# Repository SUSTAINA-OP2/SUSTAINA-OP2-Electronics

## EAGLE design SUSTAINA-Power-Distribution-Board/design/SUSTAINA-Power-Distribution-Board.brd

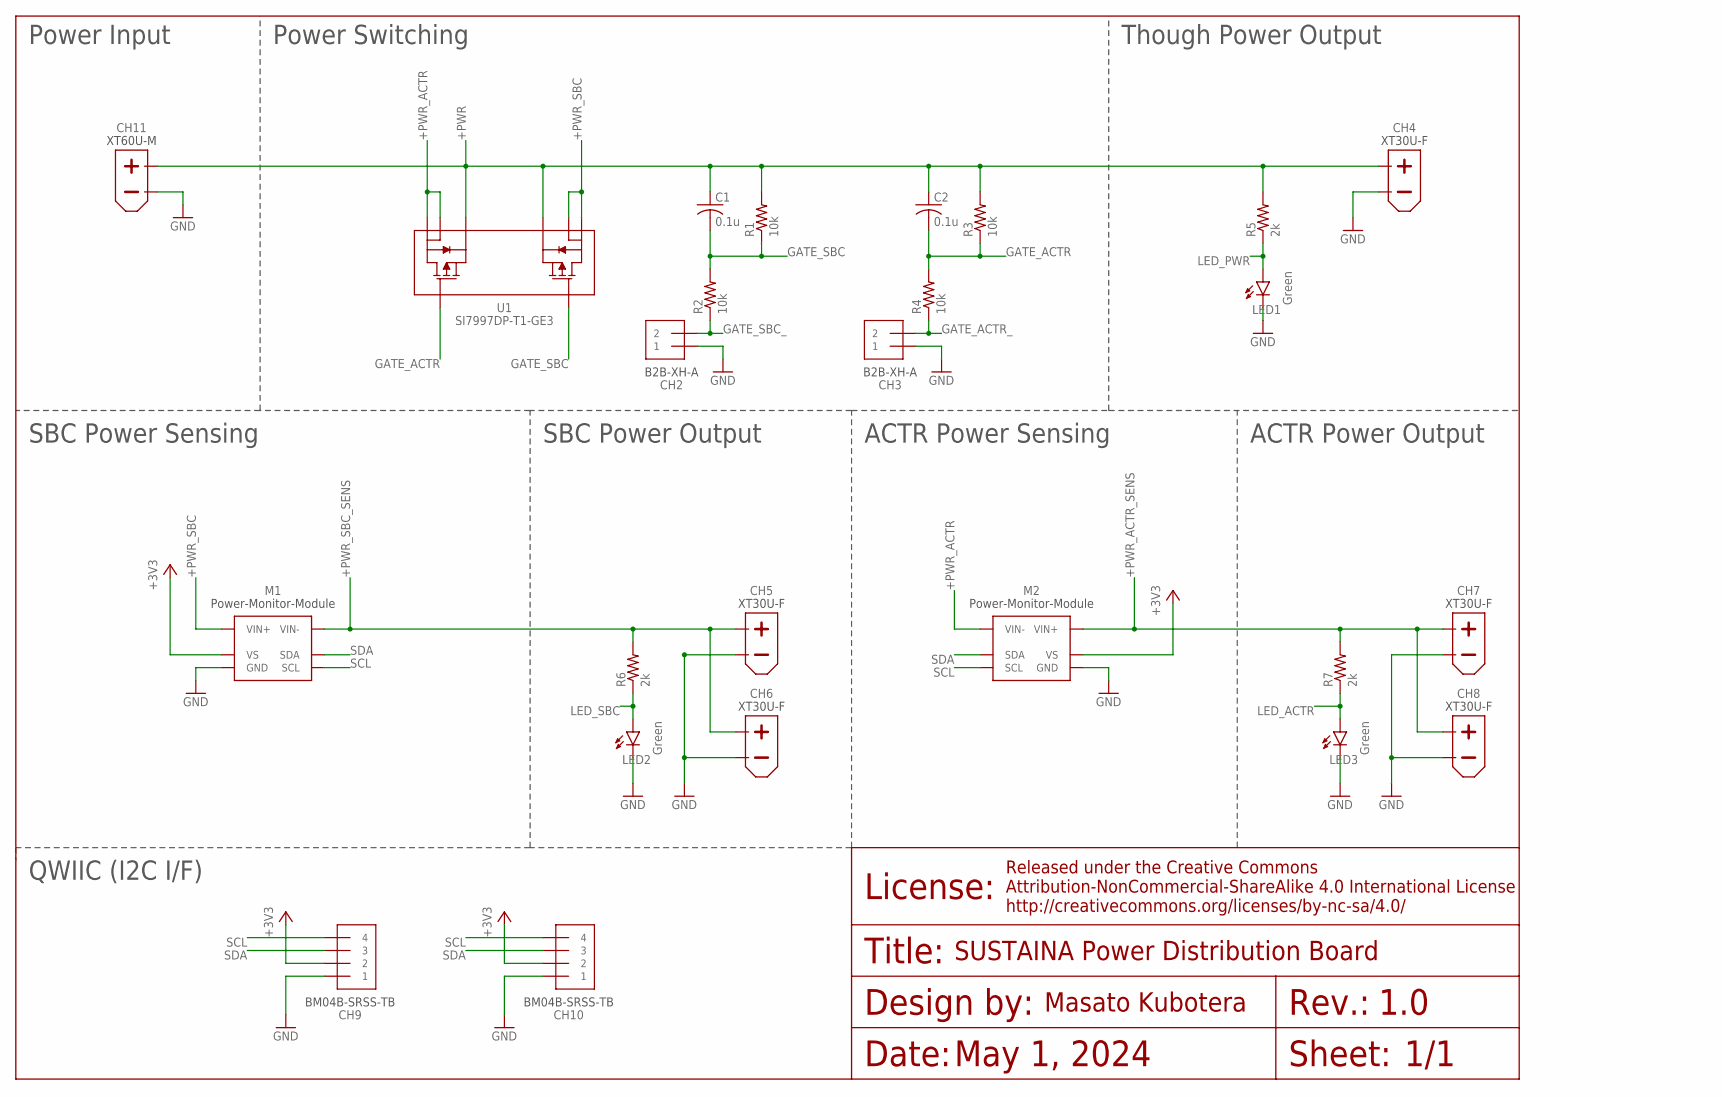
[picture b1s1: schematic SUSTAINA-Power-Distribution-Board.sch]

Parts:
C1, C2: 0.1u; C0603
CH2, CH3: B2B-XH-A
CH4, CH5, CH6, CH7, CH8: XT30U-F
CH9, CH10: BM04B-SRSS-TB
CH11: XT60U-M
LED1, LED2, LED3: Green; SML0603
M1, M2: POWER-MONITOR-MODULE
R1, R2, R3, R4: 10k; R0603
R5, R6, R7: 2k; R0603
U1: SI7997DP-T1-GE3; POWERPAK_SO-8_VIS

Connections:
+3V3: CH9.2, CH10.2, M1.VS, M2.VS
+PWR: C1.1, C2.1, CH4.+, CH11.+, R1.2, R3.2, R5.2, U1.1 (S1), U1.3 (S2)
+PWR_ACTR: M2.VIN-1 (VIN-), M2.VIN-2 (VIN-), M2.VIN-3 (VIN-), M2.VIN-4 (VIN-), M2.VIN-5 (VIN-), M2.VIN-6 (VIN-), M2.VIN-7 (VIN-), M2.VIN-8 (VIN-), M2.VIN-9 (VIN-), M2.VIN-10 (VIN-), U1.7 (D1), U1.8 (D1_2)
+PWR_ACTR_SENS: CH7.+, CH8.+, M2.VIN+1 (VIN+), M2.VIN+2 (VIN+), M2.VIN+3 (VIN+), M2.VIN+4 (VIN+), M2.VIN+5 (VIN+), M2.VIN+6 (VIN+), M2.VIN+7 (VIN+), M2.VIN+8 (VIN+), M2.VIN+9 (VIN+), M2.VIN+10 (VIN+), R7.2
+PWR_SBC: M1.VIN+1 (VIN+), M1.VIN+2 (VIN+), M1.VIN+3 (VIN+), M1.VIN+4 (VIN+), M1.VIN+5 (VIN+), M1.VIN+6 (VIN+), M1.VIN+7 (VIN+), M1.VIN+8 (VIN+), M1.VIN+9 (VIN+), M1.VIN+10 (VIN+), U1.5 (D2), U1.6 (D2_2)
+PWR_SBC_SENS: CH5.+, CH6.+, M1.VIN-1 (VIN-), M1.VIN-2 (VIN-), M1.VIN-3 (VIN-), M1.VIN-4 (VIN-), M1.VIN-5 (VIN-), M1.VIN-6 (VIN-), M1.VIN-7 (VIN-), M1.VIN-8 (VIN-), M1.VIN-9 (VIN-), M1.VIN-10 (VIN-), R6.2
GATE_ACTR: C2.2, R3.1, R4.2, U1.2 (G1)
GATE_ACTR_: CH3.2, R4.1
GATE_SBC: C1.2, R1.1, R2.2, U1.4 (G2)
GATE_SBC_: CH2.2, R2.1
GND: CH2.1, CH3.1, CH4.-, CH5.-, CH6.-, CH7.-, CH8.-, CH9.1, CH10.1, CH11.-, LED1.C, LED2.C, LED3.C, M1.GND, M2.GND
LED_ACTR: LED3.A, R7.1
LED_PWR: LED1.A, R5.1
LED_SBC: LED2.A, R6.1
SCL: CH9.4, CH10.4, M1.SCL, M2.SCL
SDA: CH9.3, CH10.3, M1.SDA, M2.SDA

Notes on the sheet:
1.0
1/1
May 1, 2024
SUSTAINA Power Distribution Board
Power Input
ACTR Power Sensing
SBC Power Sensing
QWIIC (I2C I/F)
Power Switching
Though Power Output
SBC Power Output
ACTR Power Output

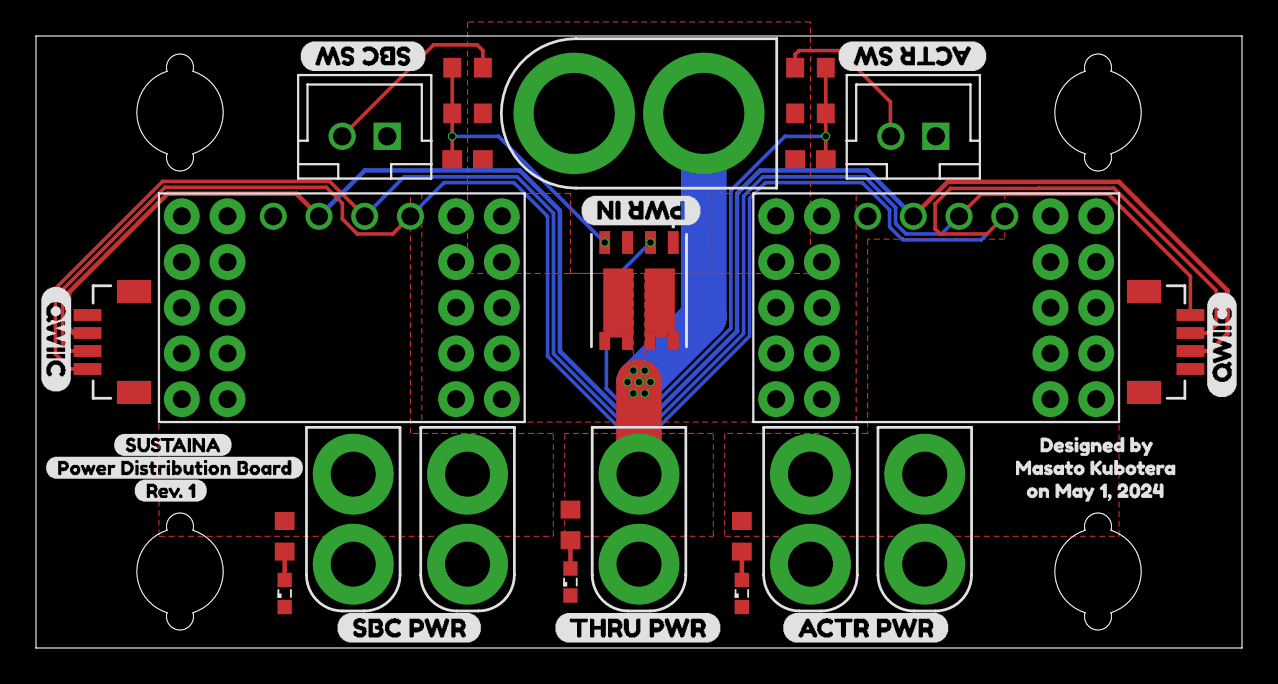
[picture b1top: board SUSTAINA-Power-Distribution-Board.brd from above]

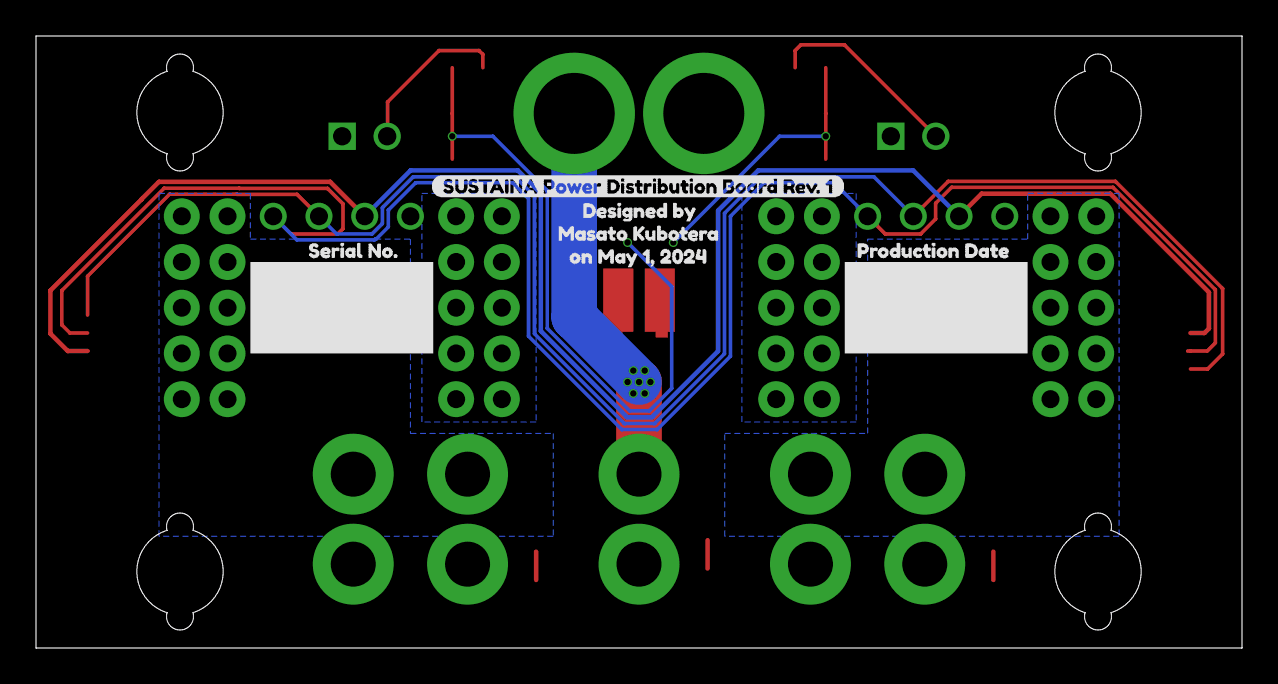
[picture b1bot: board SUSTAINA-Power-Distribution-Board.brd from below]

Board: 2 copper layers, 67.0 x 34.0 mm, 41 parts (4 on the bottom side), 16 nets.

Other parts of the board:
U$1, U$8: QWIIC
U$2: ACTR_SW
U$3: SBC_SW
U$4: ACTR_PWR
U$5: THRU_PWR
U$6: SBC_PWR
U$7: PWR_IN
U$9: PRODUCTION_DATE-0.03
U$10: SUSTAINA_POWER_DISTRIBUTION_BOARD_REV#_1-0.03
U$11, U$12: DESIGNED_BY_MASATO_KUBOTERA_ON_MAY_1-COLUMN
U$14: REV#_1-0.03
U$15: SUSTAINA-0.03
U$18: POWER_DISTRIBUTION_BOARD-0.03
U$19: SERIAL_NO#-0.03

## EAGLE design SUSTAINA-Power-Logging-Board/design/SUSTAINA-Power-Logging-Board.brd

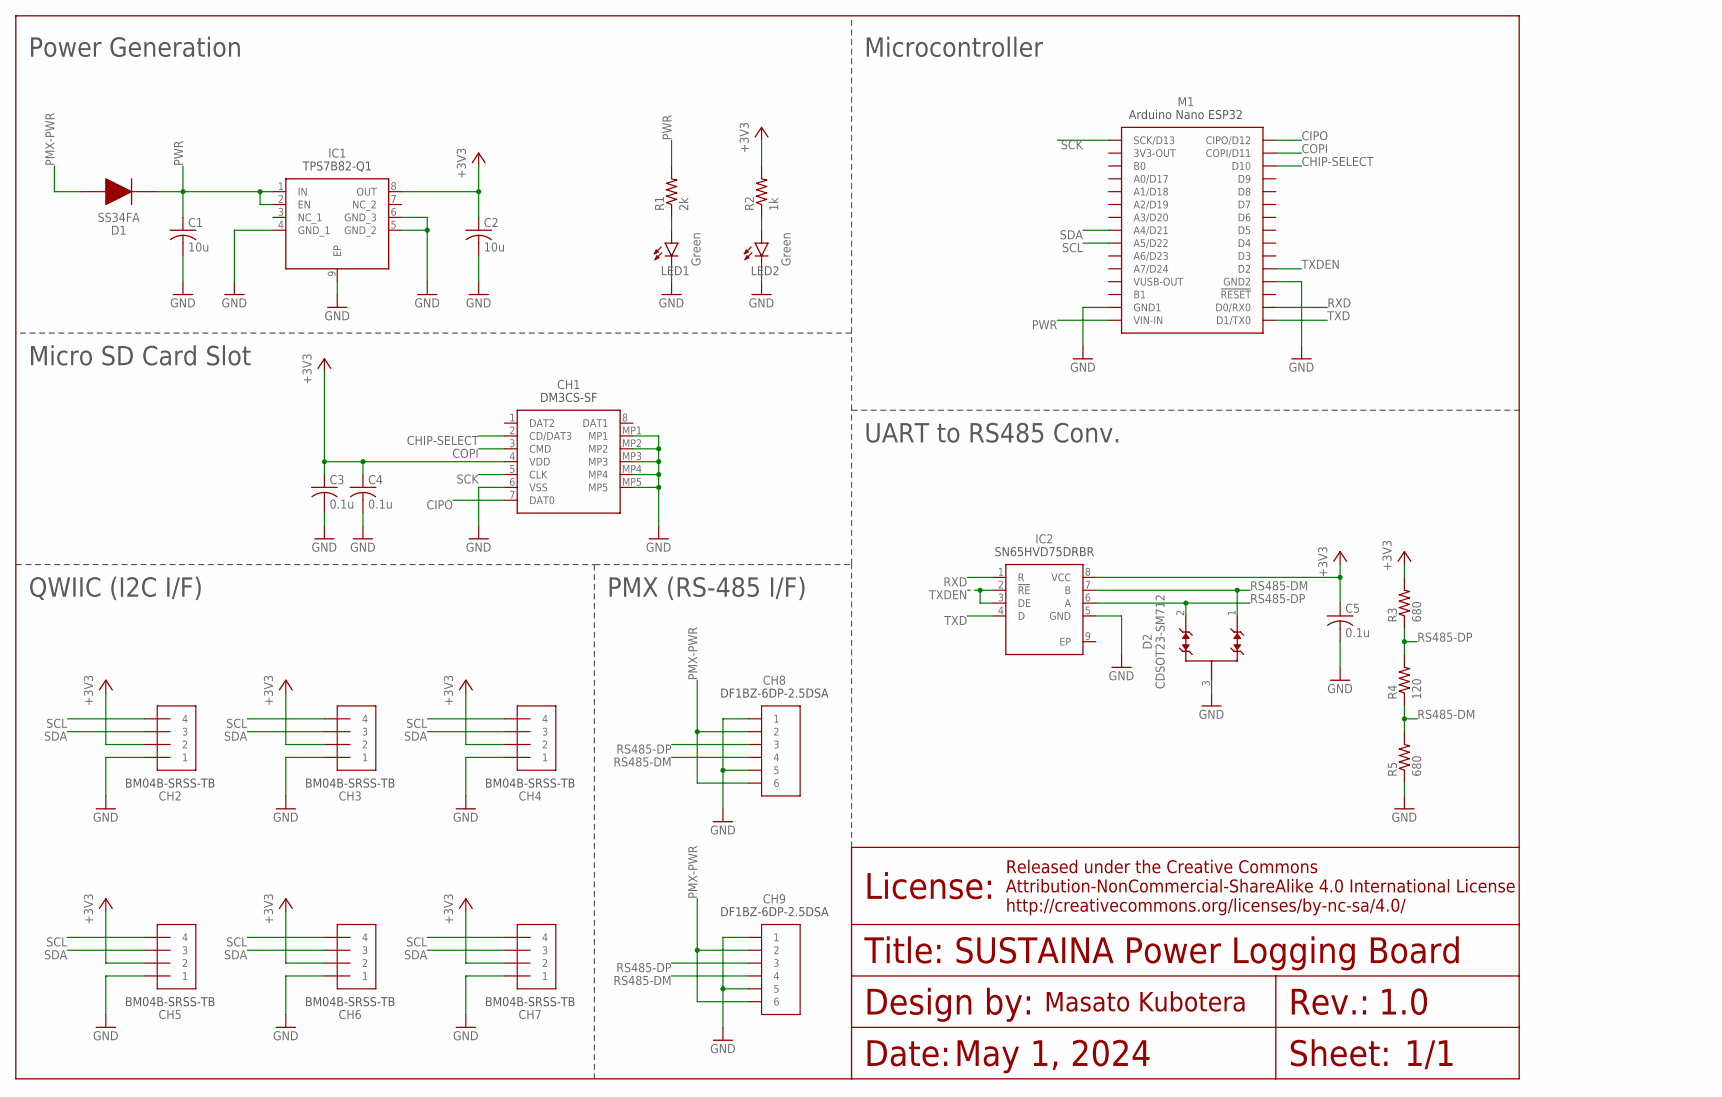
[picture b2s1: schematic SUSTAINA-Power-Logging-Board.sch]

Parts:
C1, C2: 10u; C0603
C3, C4, C5: 0.1u; C0603
CH1: DM3CS-SF
CH2, CH3, CH4, CH5, CH6, CH7: BM04B-SRSS-TB
CH8, CH9: DF1BZ-6DP-25DSA
D1: SS34FA
D2: CDSOT23-SM712; SOT-23-3
IC1: TPS7B82-Q1; SOP65P490X110-9N
IC2: SN65HVD75DRBR; SON65P300X300X100-9N
LED1, LED2: Green; SML0603
M1: NANO-ESP32
R1: 2k; R0603
R2: 1k; R0603
R3, R5: 680; R0603
R4: 120; R0603

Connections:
+3V3: C2.1, C3.1, C4.1, C5.1, CH1.4 (VDD), CH2.2, CH3.2, CH4.2, CH5.2, CH6.2, CH7.2, IC1.8 (OUT), IC2.8 (VCC), R2.2, R3.2
CHIP-SELECT: CH1.2 (CD/DAT3), M1.D10
CIPO: CH1.7 (DAT0), M1.CIPO/D12
COPI: CH1.3 (CMD), M1.COPI/D11
GND: C1.2, C2.2, C3.2, C4.2, C5.2, CH1.6 (VSS), CH1.MP1, CH1.MP2, CH1.MP3, CH1.MP4, CH1.MP5, CH2.1, CH3.1, CH4.1, CH5.1, CH6.1, CH7.1, CH8.1, CH8.5, CH9.1, CH9.5, D2.3, IC1.4 (GND_1), IC1.5 (GND_2), IC1.6 (GND_3), IC1.9 (EP), IC2.5 (GND), LED1.C, LED2.C, M1.GND1, M1.GND2, R5.1
LED-3V3: LED2.A, R2.1
LED-PWR: LED1.A, R1.1
PMX-PWR: CH8.2, CH8.6, CH9.2, CH9.6, D1.2
PWR: C1.1, D1.1, IC1.1 (IN), IC1.2 (EN), M1.VIN-IN, R1.2
RS485-DM: CH8.4, CH9.4, D2.1, IC2.7 (B), R4.1, R5.2
RS485-DP: CH8.3, CH9.3, D2.2, IC2.6 (A), R3.1, R4.2
RXD: IC2.1 (R), M1.D0/RX0
SCK: CH1.5 (CLK), M1.SCK/D13
SCL: CH2.4, CH3.4, CH4.4, CH5.4, CH6.4, CH7.4, M1.A5/D22
SDA: CH2.3, CH3.3, CH4.3, CH5.3, CH6.3, CH7.3, M1.A4/D21
TXD: IC2.4 (D), M1.D1/TX0
TXDEN: IC2.2 (!RE), IC2.3 (DE), M1.D2

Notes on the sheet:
Power Generation
Microcontroller
PMX (RS-485 I/F)
UART to RS485 Conv.
1.0
1/1
May 1, 2024
SUSTAINA Power Logging Board
Micro SD Card Slot
QWIIC (I2C I/F)

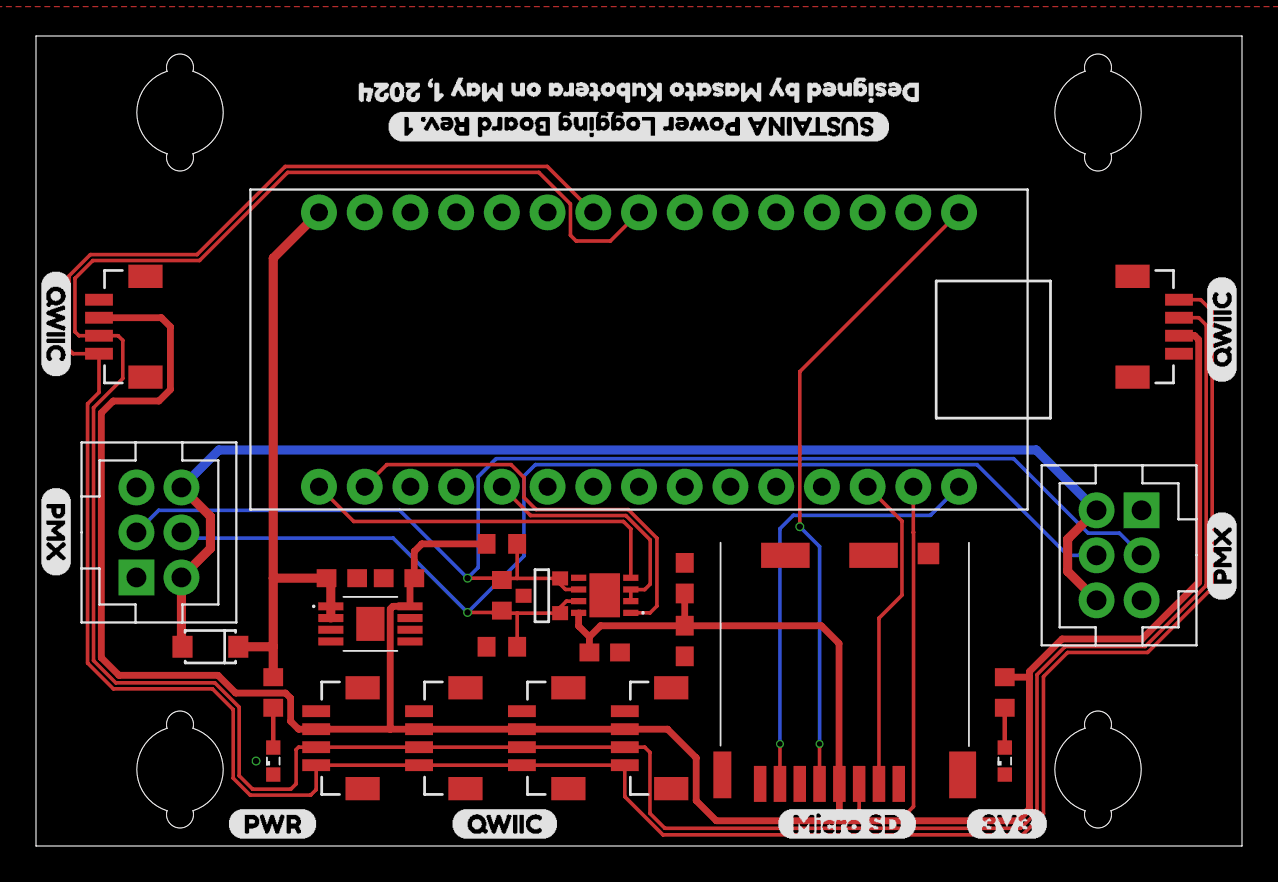
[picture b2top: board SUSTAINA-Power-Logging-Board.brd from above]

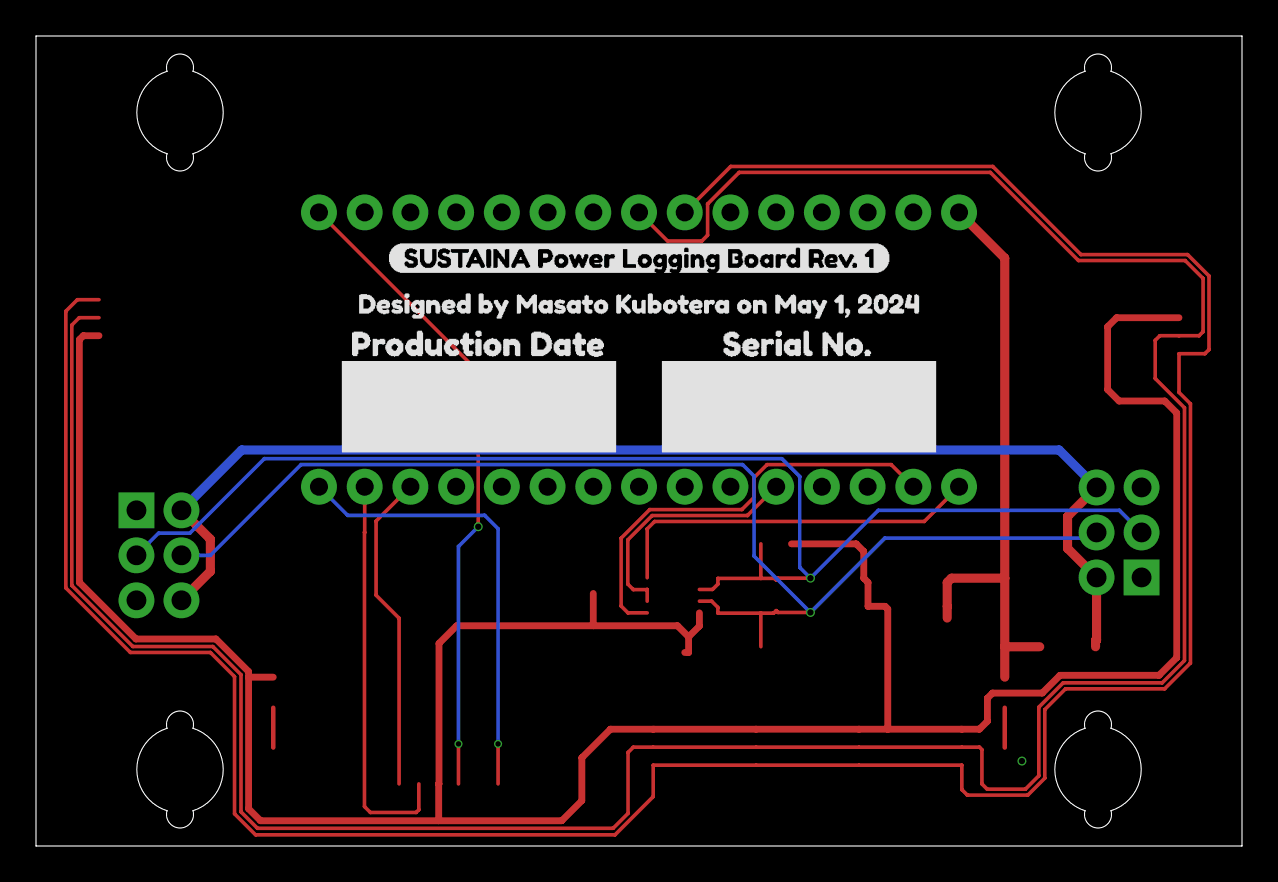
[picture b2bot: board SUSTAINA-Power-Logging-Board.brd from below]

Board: 2 copper layers, 67.0 x 45.0 mm, 40 parts (4 on the bottom side), 17 nets.

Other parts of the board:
U$1, U$12: PMX
U$2: 3V3
U$3: MICRO_SD
U$4, U$5, U$10: QWIIC
U$6: PRODUCTION_DATE0
U$7: SERIAL_NO#0
U$8, U$9: DESIGNED_BY_MASATO_KUBOTERA_ON_MAY_1
U$11, U$14: SUSTAINA_POWER_LOGGING_BOARD_REV#_1
U$13: PWR

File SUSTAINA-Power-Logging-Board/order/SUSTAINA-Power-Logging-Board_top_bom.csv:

Comment,Designator,Footprint,LCSC Part #
0.1u,C3 C4 C5,C0603,C80516
1k,R2,R0603,C22548
2k,R1,R0603,C105576
10u,C1 C2,C0603,C86275
120,R4,R0603,C114640
680,R3 R5,R0603,C112310
BM04B-SRSS-TB,CH2 CH3 CH4 CH5 CH6 CH7,BM04B-SRSS-TB,C160390
DM3CS-SF,CH1,DM3CS-SF,C202111
Green,LED1 LED2,SML0603,C2922668
SN65HVD75DRBR,IC2,SON65P300X300X100-9N,C98708
SS34FA,D1,SS34FA,C719833
TPS7B82-Q1,IC1,SOP65P490X110-9N,C5220182
CDSOT23-SM712,D2 ,CDSOT23-SM712,C404012

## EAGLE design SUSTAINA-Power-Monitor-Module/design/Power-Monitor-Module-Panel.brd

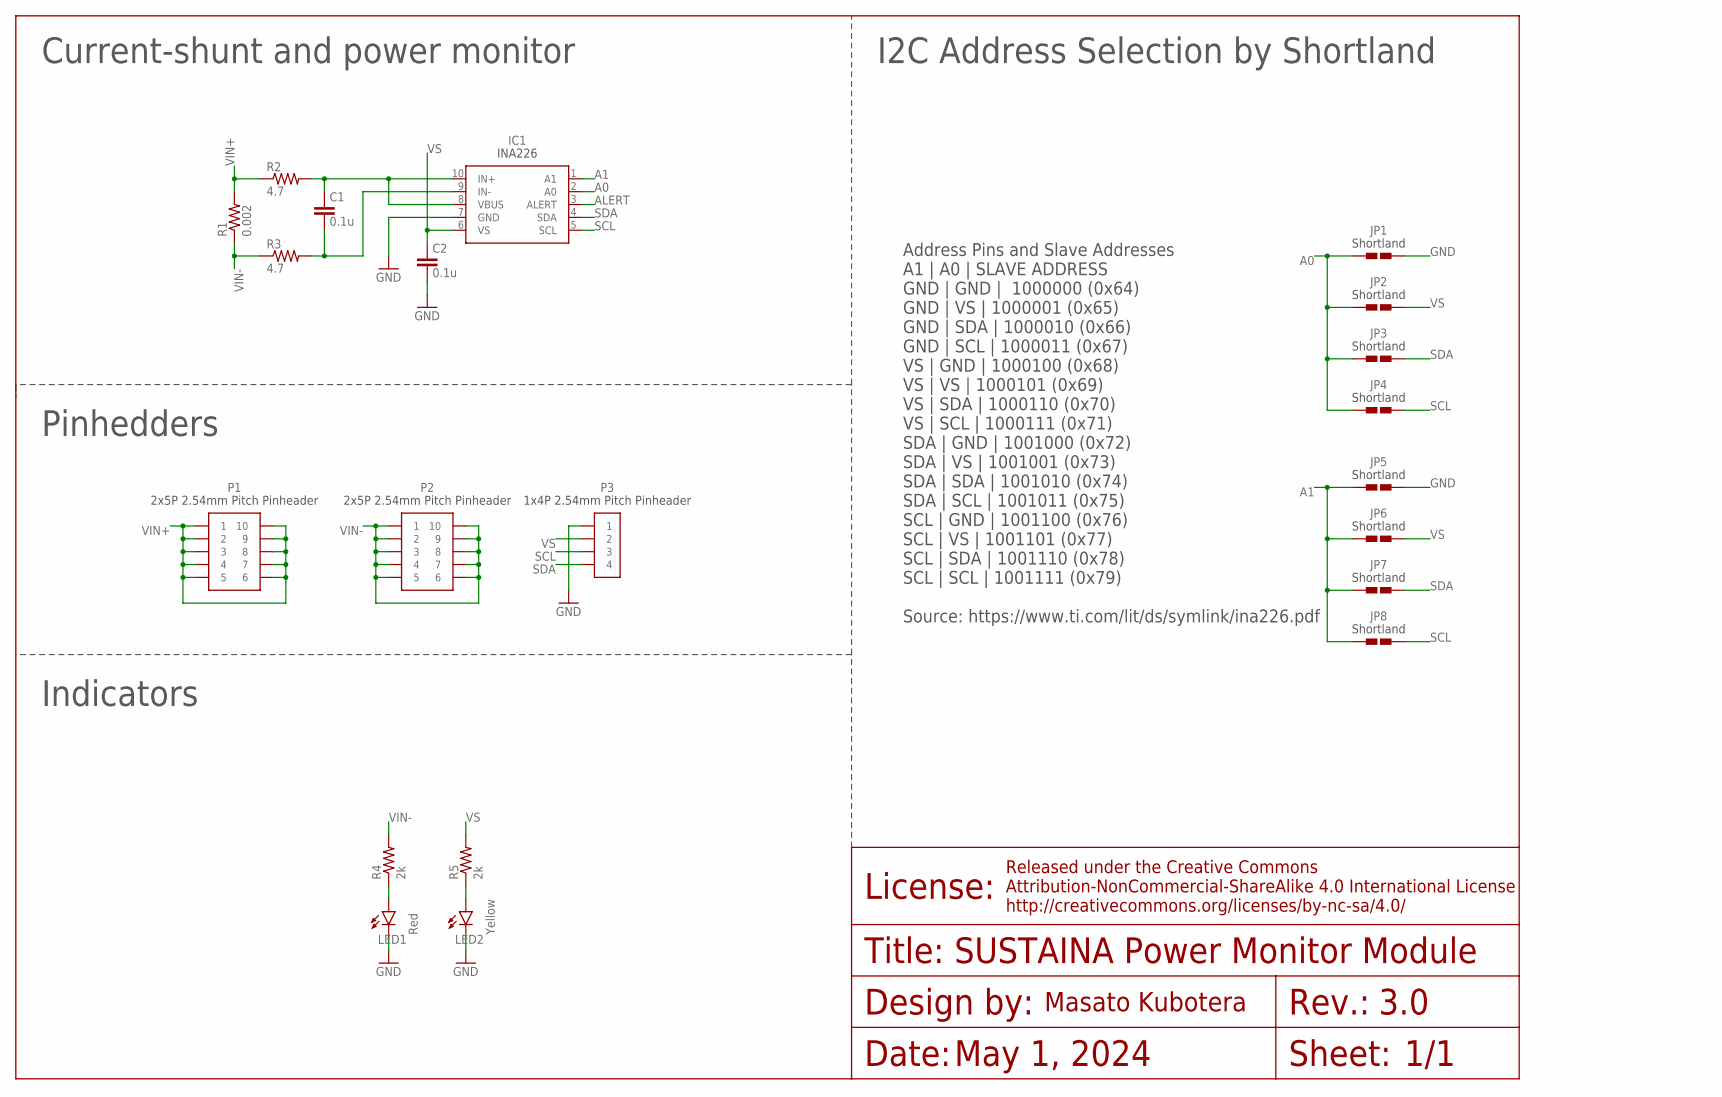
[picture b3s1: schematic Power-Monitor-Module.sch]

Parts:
C1, C2: 0.1u; C0402
IC1: INA226; MSOP-10
JP1, JP2, JP3, JP4, JP5, JP6, JP7, JP8: SHORTLAND
LED1: Red; SML0603
LED2: Yellow; SML0603
P1, P2: 2X5P
P3: 1X4P
R1: 0.002; R2512
R2, R3: 4.7; R0402
R4, R5: 2k; R0402

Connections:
A0: IC1.2 (A0), JP1.1, JP2.1, JP3.1, JP4.1
A1: IC1.1 (A1), JP5.1, JP6.1, JP7.1, JP8.1
ALERT: IC1.3 (ALERT)
GND: C2.2, IC1.7 (GND), JP1.2, JP5.2, LED1.C, LED2.C, P3.1
IN+: C1.1, IC1.8 (VBUS), IC1.10 (IN+), R2.2
IN-: C1.2, IC1.9 (IN-), R3.2
LED1_: LED1.A, R4.1
LED2: LED2.A, R5.1
SCL: IC1.5 (SCL), JP4.2, JP8.2, P3.3
SDA: IC1.4 (SDA), JP3.2, JP7.2, P3.4
VIN+: P1.1, P1.2, P1.3, P1.4, P1.5, P1.6, P1.7, P1.8, P1.9, P1.10, R1.2, R2.1
VIN-: P2.1, P2.2, P2.3, P2.4, P2.5, P2.6, P2.7, P2.8, P2.9, P2.10, R1.1, R3.1, R4.2
VS: C2.1, IC1.6 (VS), JP2.2, JP6.2, P3.2, R5.2

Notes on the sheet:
I2C Address Selection by Shortland
Pinhedders
Current-shunt and power monitor
May 1, 2024
SUSTAINA Power Monitor Module
3.0
1/1
Address Pins and Slave Addresses A1 | A0 | SLAVE ADDRESS GND | GND | 1000000 (0x64) GND | VS | 1000001 (0x65) GND | SDA | 1000010 (0x66) GND | SCL | 1000011 (0x67) VS | GND | 1000100 (0x68) VS | VS | 1000101 (0x69) VS | SDA | 1000110 (0x70) VS | SCL | 1000111 (0x71) SDA | GND | 1001000 (0x72) SDA |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
Indicators

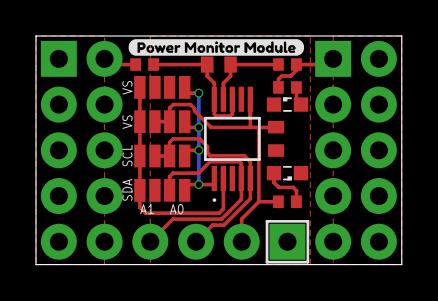
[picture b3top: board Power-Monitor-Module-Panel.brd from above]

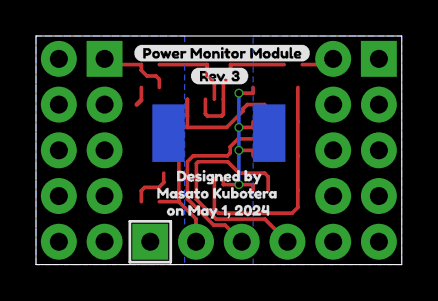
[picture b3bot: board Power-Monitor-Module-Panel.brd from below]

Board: 2 copper layers, 20.3 x 12.7 mm, 25 parts (4 on the bottom side), 12 nets.

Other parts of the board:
U$1, U$2: POWER_MONITOR_MODULE
U$3: REV#_3
U$5: DESIGNED_BY_MASATO_KUBOTERA_ON_MAY_1-0.0225

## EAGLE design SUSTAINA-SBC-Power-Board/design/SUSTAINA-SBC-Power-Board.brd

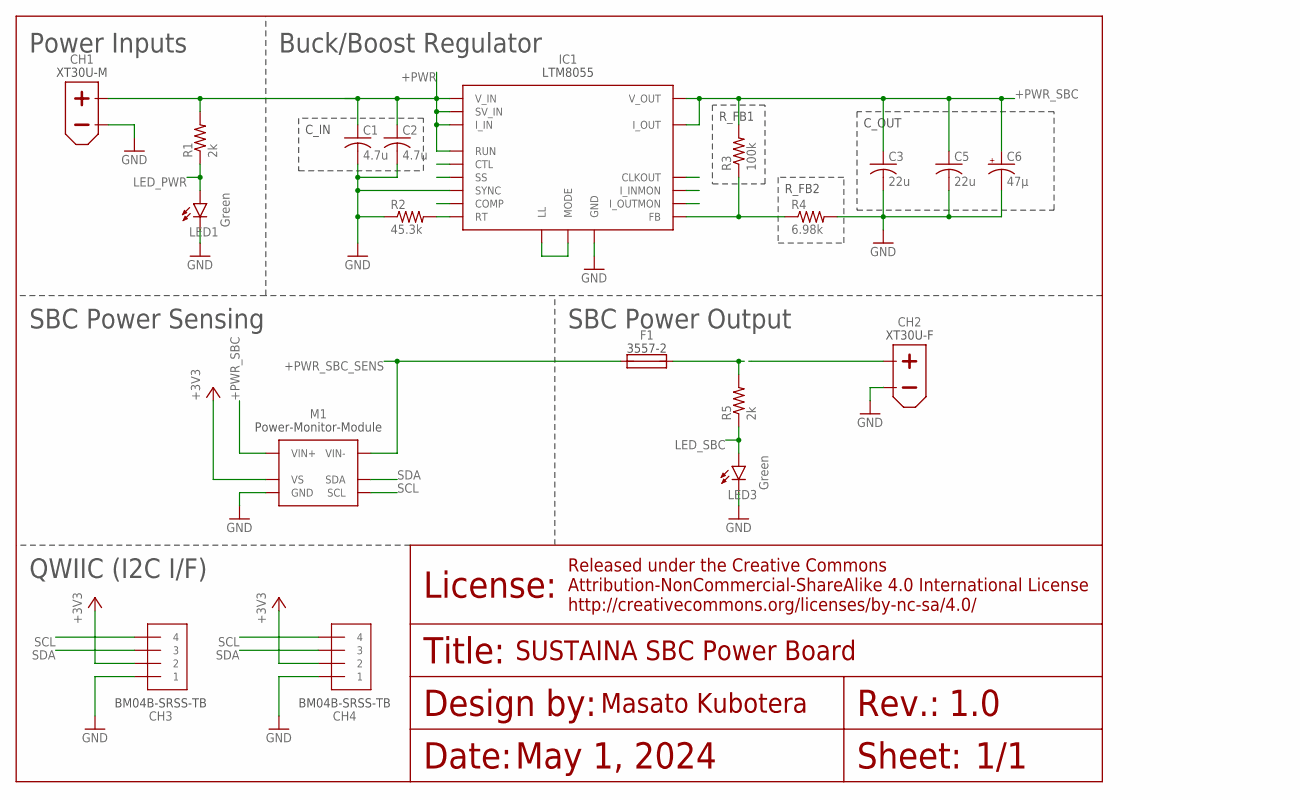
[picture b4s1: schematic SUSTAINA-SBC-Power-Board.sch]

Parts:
C1, C2: 4.7u; C0805
C3, C5: 22u; C0805
C6: 47µ; D/7343-31R
CH1: XT30U-M
CH2: XT30U-F
CH3, CH4: BM04B-SRSS-TB
F1: 3557-2
IC1: LTM8055
LED1, LED3: Green; SML0603
M1: POWER-MONITOR-MODULE
R1, R5: 2k; R0603
R2: 45.3k; R0603
R3: 100k; R0603
R4: 6.98k; R0603

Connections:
+3V3: CH3.2, CH4.2, M1.VS
+PWR: C1.1, C2.1, CH1.+, IC1.F10 (SV_IN), IC1.F11 (SV_IN), IC1.G10 (V_IN), IC1.G11 (V_IN), IC1.H10 (V_IN), IC1.H11 (V_IN), IC1.J10 (V_IN), IC1.J11 (V_IN), IC1.K10 (V_IN), IC1.K11 (V_IN), IC1.L4 (RUN), IC1.L9 (I_IN), IC1.L10 (V_IN), IC1.L11 (V_IN), R1.2
+PWR_SBC: C3.1, C5.1, C6.+, IC1.A1 (V_OUT), IC1.A2 (V_OUT), IC1.A3 (V_OUT), IC1.A4 (V_OUT), IC1.A5 (V_OUT), IC1.A6 (V_OUT), IC1.B1 (V_OUT), IC1.B2 (V_OUT), IC1.B3 (V_OUT), IC1.B4 (V_OUT), IC1.B5 (V_OUT), IC1.B6 (V_OUT), IC1.C1 (V_OUT), IC1.C2 (V_OUT), IC1.C3 (V_OUT), IC1.C4 (V_OUT), IC1.C5 (V_OUT), IC1.C6 (V_OUT), IC1.D1 (I_OUT), M1.VIN+1 (VIN+), M1.VIN+2 (VIN+), M1.VIN+3 (VIN+), M1.VIN+4 (VIN+), M1.VIN+5 (VIN+), M1.VIN+6 (VIN+), M1.VIN+7 (VIN+), M1.VIN+8 (VIN+), M1.VIN+9 (VIN+), M1.VIN+10 (VIN+), R3.2
+PWR_SBC_OUT: CH2.+, F1.3 (2), F1.4 (2), R5.2
+PWR_SBC_SENS: F1.1, F1.2 (1), M1.VIN-1 (VIN-), M1.VIN-2 (VIN-), M1.VIN-3 (VIN-), M1.VIN-4 (VIN-), M1.VIN-5 (VIN-), M1.VIN-6 (VIN-), M1.VIN-7 (VIN-), M1.VIN-8 (VIN-), M1.VIN-9 (VIN-), M1.VIN-10 (VIN-)
CLKOUT: IC1.G1 (CLKOUT)
COMP: IC1.J2 (COMP)
FB: IC1.J1 (FB), R3.1, R4.1
GND: C1.2, C2.2, C3.2, C5.2, C6.-, CH1.-, CH2.-, CH3.1, CH4.1, IC1.A7 (GND), IC1.A8 (GND), IC1.A9 (GND), IC1.A10 (GND), IC1.A11 (GND), IC1.B7 (GND), IC1.B8 (GND), IC1.B9 (GND), IC1.B10 (GND), IC1.B11 (GND), IC1.C7 (GND), IC1.C8 (GND), IC1.C9 (GND), IC1.C10 (GND), IC1.C11 (GND), IC1.D2 (GND), IC1.D3 (GND), IC1.D4 (GND), IC1.D5 (GND), IC1.D6 (GND), IC1.D7 (GND), IC1.D8 (GND), IC1.D9 (GND), IC1.D10 (GND), IC1.D11 (GND), IC1.E1 (GND), IC1.E2 (GND), IC1.E3 (GND), IC1.E4 (GND), IC1.E5 (GND), IC1.E6 (GND), IC1.E7 (GND), IC1.E8 (GND), IC1.E9 (GND), IC1.E10 (GND), IC1.E11 (GND), IC1.F2 (GND), IC1.F3 (GND), IC1.F4 (GND), IC1.F5 (GND), IC1.F6 (GND), IC1.F7 (GND), IC1.F8 (GND), IC1.F9 (GND), IC1.G3 (GND), IC1.G4 (GND), IC1.G5 (GND), IC1.G6 (GND), IC1.G7 (GND), IC1.G8 (GND), IC1.G9 (GND), IC1.H2 (SYNC), IC1.H3 (GND), IC1.H4 (GND), IC1.H5 (GND), IC1.H6 (GND), IC1.H7 (GND), IC1.H8 (GND), IC1.H9 (GND), IC1.J3 (GND), IC1.J4 (GND), IC1.J5 (GND), IC1.J6 (GND), IC1.J7 (GND), IC1.J8 (GND), IC1.J9 (GND), IC1.K3 (GND), IC1.K4 (GND), IC1.K5 (GND), IC1.K6 (GND), IC1.K7 (GND), IC1.K8 (GND), IC1.K9 (GND), IC1.L1 (GND), IC1.L5 (GND), IC1.L6 (GND), IC1.L7 (GND), IC1.L8 (GND), LED1.C, LED3.C, M1.GND, R2.1, R4.2
I_INMON: IC1.L3 (I_INMON)
I_OUTMON: IC1.L2 (I_OUTMON)
LED_PWR: LED1.A, R1.1
LED_SBC: LED3.A, R5.1
MODE: IC1.F1 (LL), IC1.G2 (MODE)
RT: IC1.H1 (RT), R2.2
SCL: CH3.4, CH4.4, M1.SCL
SDA: CH3.3, CH4.3, M1.SDA
SS: IC1.K1 (SS)
STL: IC1.K2 (CTL)

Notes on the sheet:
1.0
1/1
May 1, 2024
SUSTAINA SBC Power Board
Power Inputs
SBC Power Sensing
Buck/Boost Regulator
C_IN
C_OUT
R_FB1
R_FB2
QWIIC (I2C I/F)
SBC Power Output

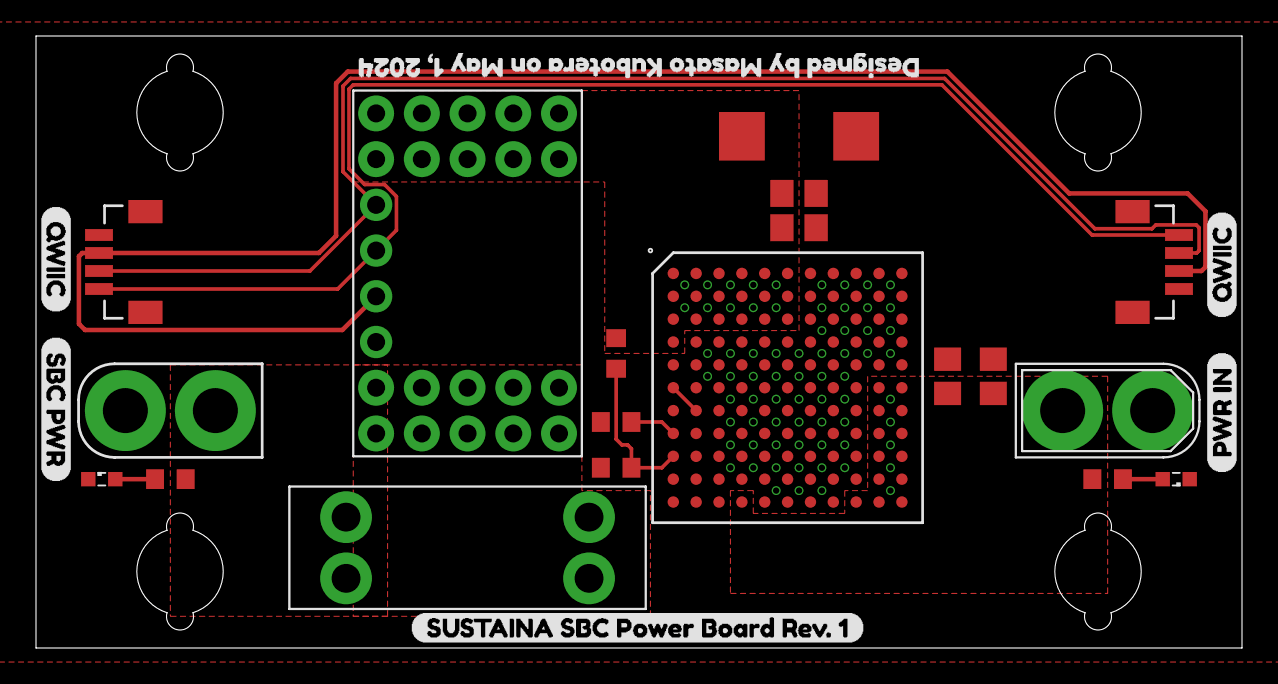
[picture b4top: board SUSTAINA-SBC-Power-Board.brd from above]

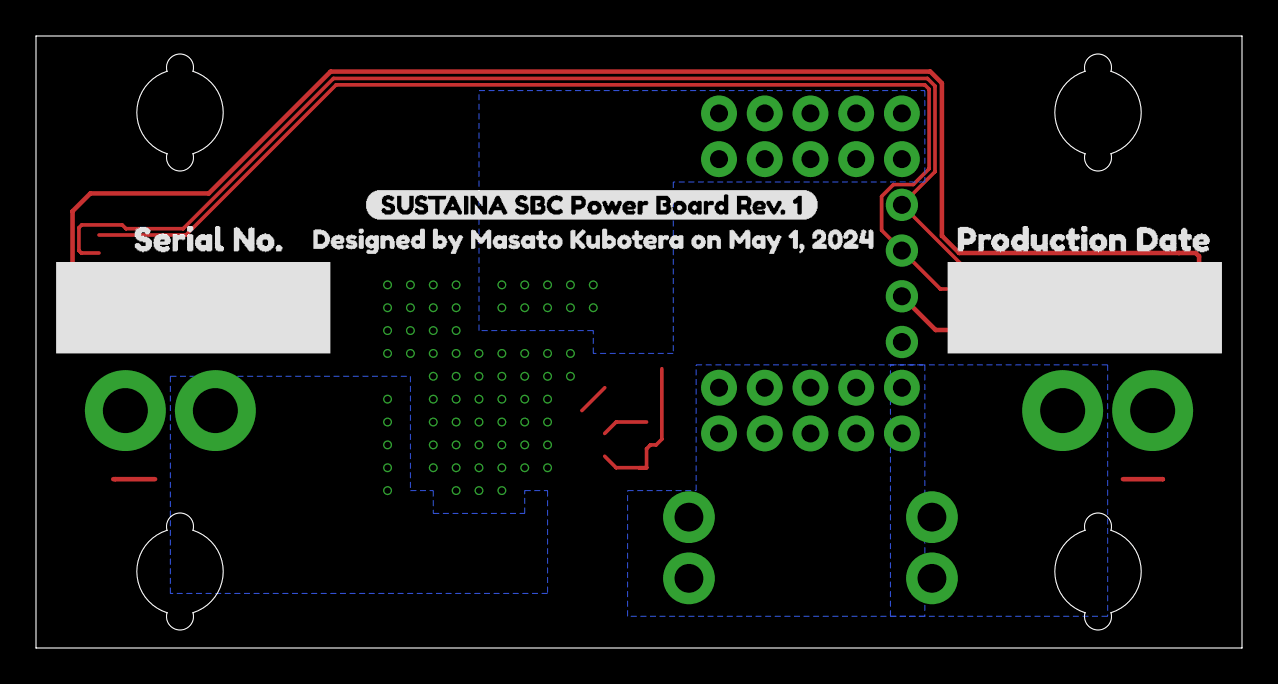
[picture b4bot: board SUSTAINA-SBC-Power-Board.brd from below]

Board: 2 copper layers, 67.0 x 34.0 mm, 29 parts (4 on the bottom side), 13 nets.

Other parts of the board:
U$1: PWR_IN
U$2: SBC_PWR
U$3, U$4: QWIIC
U$5, U$7: DESIGNED_BY_MASATO_KUBOTERA_ON_MAY_1
U$6, U$8: SUSTAINA_SBC_POWER_BOARD_REV#_1
U$9: PRODUCTION_DATE0
U$10: SERIAL_NO#0

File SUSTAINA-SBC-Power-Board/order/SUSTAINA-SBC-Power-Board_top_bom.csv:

Comment,Designator,Footprint,LCSC Part #
2k,R1 R5,R0603,
4.7u,C1 C2,C0805,
6.98k,R4,R0603,
22u,C3 C5,C0805,
45.3k,R2,R0603,
47µ,C6,D/7343-31R,
100k,R3,R0603,
BM04B-SRSS-TB,CH3 CH4,BM04B-SRSS-TB,
Green,LED1 LED3,SML0603,
LTM8055,IC1,LTM8055,

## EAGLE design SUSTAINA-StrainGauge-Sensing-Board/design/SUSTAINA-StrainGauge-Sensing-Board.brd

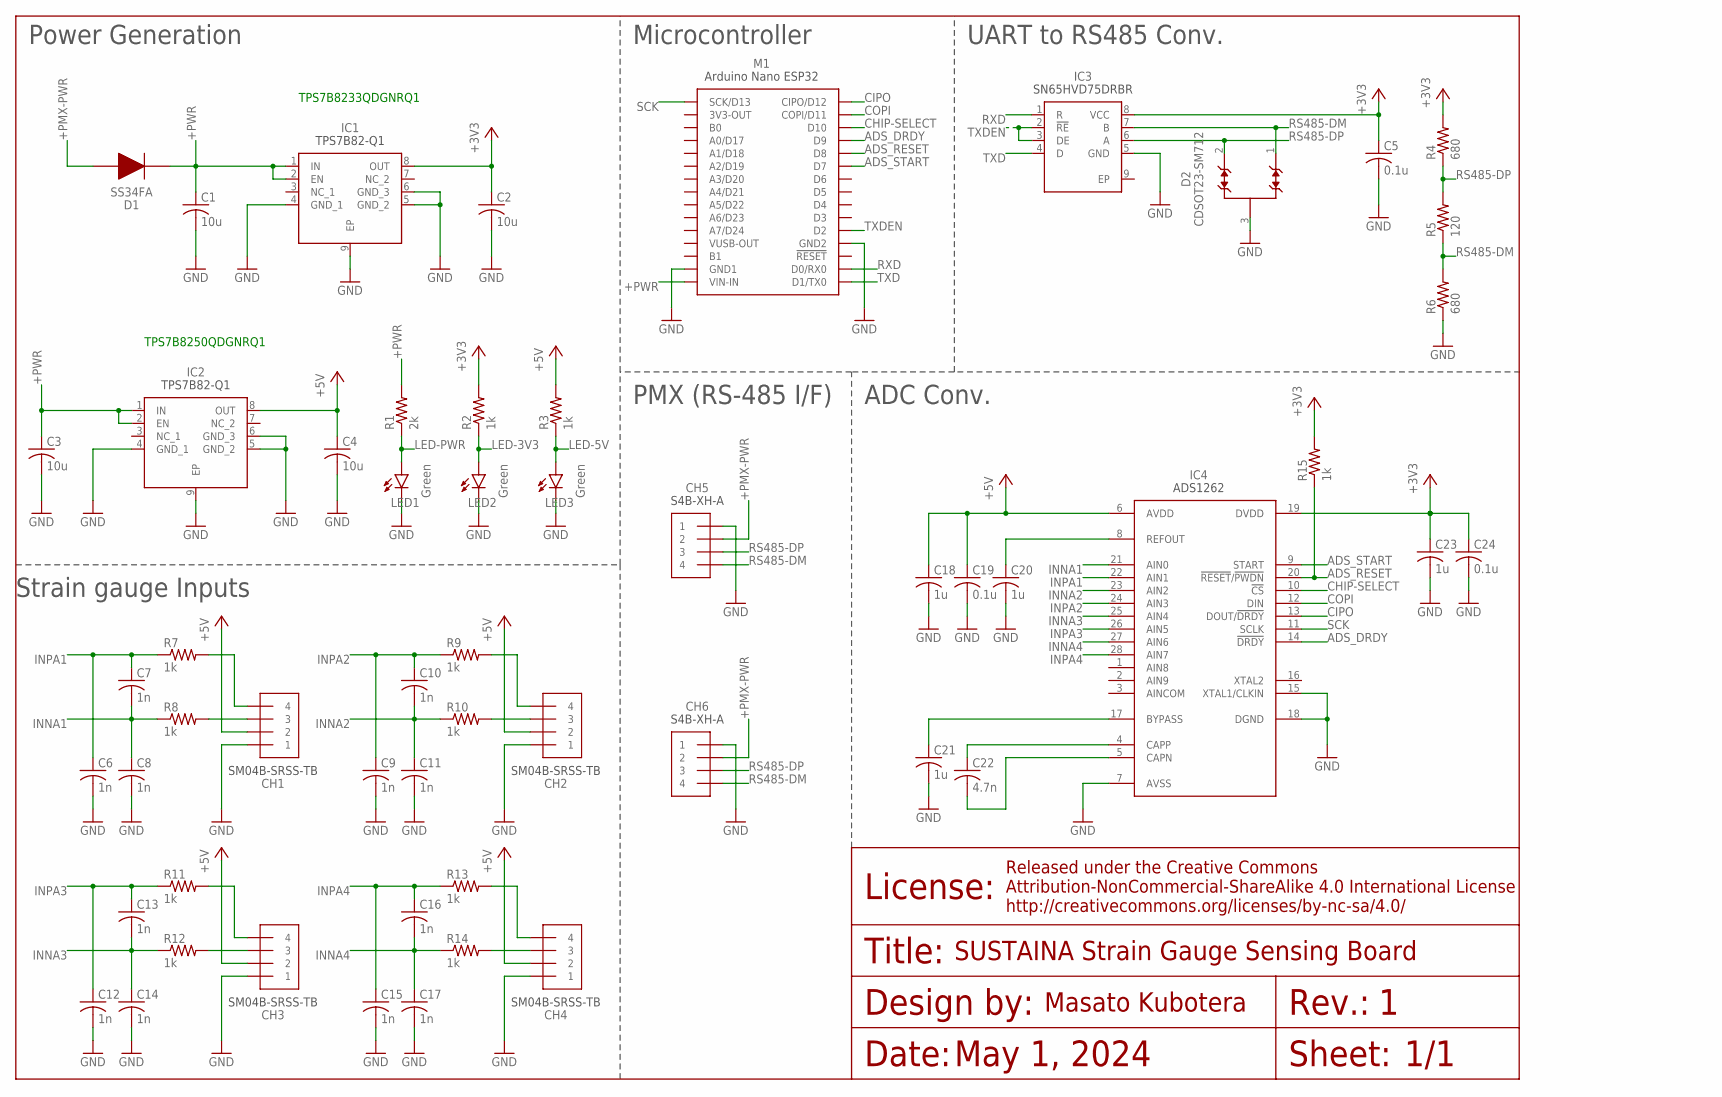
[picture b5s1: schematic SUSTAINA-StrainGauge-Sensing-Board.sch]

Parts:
C1, C2, C3, C4: 10u; C0603
C5, C19, C24: 0.1u; C0603
C6, C7, C8, C9, C10, C11, C12, C13, C14, C15, C16, C17: 1n; C0603
C18, C20, C21, C23: 1u; C0603
C22: 4.7n; C0603
CH1, CH2, CH3, CH4: SM04B-SRSS-TB
CH5, CH6: S4B-XH-A
D1: SS34FA
D2: CDSOT23-SM712; SOT-23-3
IC1, IC2: TPS7B82-Q1; SOP65P490X110-9N
IC3: SN65HVD75DRBR; SON65P300X300X100-9N
IC4: ADS1262; SOP65P640X120-28N
LED1, LED2, LED3: Green; SML0603
M1: NANO-ESP32SMD; NANO-ESP32-SMD
R1: 2k; R0603
R2, R3, R7, R8, R9, R10, R11, R12, R13, R14, R15: 1k; R0603
R4, R6: 680; R0603
R5: 120; R0603

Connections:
+3V3: C2.1, C5.1, C23.1, C24.1, IC1.8 (OUT), IC3.8 (VCC), IC4.19 (DVDD), R2.2, R4.2, R15.2
+5V: C4.1, C18.1, C19.1, CH1.2, CH2.2, CH3.2, CH4.2, IC2.8 (OUT), IC4.6 (AVDD), R3.2
+PMX-PWR: CH5.2, CH6.2, D1.2
+PWR: C1.1, C3.1, D1.1, IC1.1 (IN), IC1.2 (EN), IC2.1 (IN), IC2.2 (EN), M1.VIN-IN, R1.2
ADS_DRDY: IC4.14 (!DRDY), M1.D9
ADS_RESET: IC4.20 (!RESET!/!PWDN), M1.D8, R15.1
ADS_START: IC4.9 (START), M1.D7
BYPASS: C21.1, IC4.17 (BYPASS)
CAPN: C22.2, IC4.5 (CAPN)
CAPP: C22.1, IC4.4 (CAPP)
CHIP-SELECT: IC4.10 (!CS), M1.D10
CIPO: IC4.13 (DOUT/!DRDY), M1.CIPO/D12
COPI: IC4.12 (DIN), M1.COPI/D11
GND: C1.2, C2.2, C3.2, C4.2, C5.2, C6.2, C8.2, C9.2, C11.2, C12.2, C14.2, C15.2, C17.2, C18.2, C19.2, C20.2, C21.2, C23.2, C24.2, CH1.1, CH2.1, CH3.1, CH4.1, CH5.1, CH6.1, D2.3, IC1.4 (GND_1), IC1.5 (GND_2), IC1.6 (GND_3), IC1.9 (EP), IC2.4 (GND_1), IC2.5 (GND_2), IC2.6 (GND_3), IC2.9 (EP), IC3.5 (GND), IC4.7 (AVSS), IC4.15 (XTAL1/CLKIN), IC4.18 (DGND), LED1.C, LED2.C, LED3.C, M1.GND1, M1.GND2, R6.1
INNA1: C7.2, C8.1, IC4.21 (AIN0), R8.1
INNA1_: CH1.3, R8.2
INNA2: C10.2, C11.1, IC4.23 (AIN2), R10.1
INNA2_: CH2.3, R10.2
INNA3: C13.2, C14.1, IC4.25 (AIN4), R12.1
INNA3_: CH3.3, R12.2
INNA4: C16.2, C17.1, IC4.27 (AIN6), R14.1
INNA4_: CH4.3, R14.2
INPA1: C6.1, C7.1, IC4.22 (AIN1), R7.1
INPA1_: CH1.4, R7.2
INPA2: C9.1, C10.1, IC4.24 (AIN3), R9.1
INPA2_: CH2.4, R9.2
INPA3: C12.1, C13.1, IC4.26 (AIN5), R11.1
INPA3_: CH3.4, R11.2
INPA4: C15.1, C16.1, IC4.28 (AIN7), R13.1
INPA4_: CH4.4, R13.2
LED-3V3: LED2.A, R2.1
LED-5V: LED3.A, R3.1
LED-PWR: LED1.A, R1.1
REFOUT: C20.1, IC4.8 (REFOUT)
RS485-DM: CH5.4, CH6.4, D2.1, IC3.7 (B), R5.1, R6.2
RS485-DP: CH5.3, CH6.3, D2.2, IC3.6 (A), R4.1, R5.2
RXD: IC3.1 (R), M1.D0/RX0
SCK: IC4.11 (SCLK), M1.SCK/D13
TXD: IC3.4 (D), M1.D1/TX0
TXDEN: IC3.2 (!RE), IC3.3 (DE), M1.D2

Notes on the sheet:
1/1
May 1, 2024
SUSTAINA Strain Gauge Sensing Board
TPS7B8233QDGNRQ1
TPS7B8250QDGNRQ1
Power Generation
UART to RS485 Conv.
Microcontroller
PMX (RS-485 I/F)
ADC Conv.
Strain gauge Inputs

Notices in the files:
parts and their libraries:
COPYRIGHT: Copyright (C) 2024 Ultra Librarian. All rights reserved.
Frames: Released under the Creative Commons
Attribution-NonCommercial-ShareAlike 4.0 International License
http://creativecommons.org/licenses/by-nc-sa/4.0
